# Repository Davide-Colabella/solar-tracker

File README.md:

# Solar Tracker (Arduino UNO Q)

App per Arduino App Lab: pannello a 2 assi (azimut + pitch) che insegue il sole,
si apre quando alla pianta che ha sotto arriva poca luce (fotoresistore),
riconosce la pianta e il suo stato di salute da una foto e la innaffia dal
serbatoio di raccolta quando ne ha bisogno. Una pagina web mostra tutto e
permette di muovere il pannello a mano.

## Sito di presentazione

La landing page Solar Tracker in stile COESA Energy è in [`docs/`](docs/index.html), con immagini e font locali. È distinta dall'interfaccia Arduino in `assets/index.html`.

Indirizzo previsto su GitHub Pages: [davide-colabella.github.io/solar-tracker/](https://davide-colabella.github.io/solar-tracker/).

Per attivare la pubblicazione, un amministratore o un utente con il permesso di gestire GitHub Pages deve aprire **Settings → Pages**, selezionare **Deploy from a branch**, poi **main → /docs → Save**. Il file `.nojekyll` permette di pubblicare direttamente i file statici. I successivi push dei file in `docs/` aggiornano il sito automaticamente.

Per l'anteprima locale: `python3 -m http.server 4173 --directory docs --bind 127.0.0.1`.

La pagina presenta un concept di servizio. La tabella e il configuratore usano le stime dell’analisi economica HackTurin di Davide Colabella (11 ottobre 2026, pp. 5–8): kit principale 349 €, satellite 149 €, software opzionale 48 €/anno, IVA esclusa e pannelli del cliente. Verifica, smontaggio e posa restano da quotare. La torta riguarda un ordine tipo di 4 pannelli: ricavi 796 €, produzione 440,10 €, commissione installatore 119,40 €, altri costi variabili 60 €, margine di contribuzione 176,50 € prima di costi fissi e imposte. Il margine non è un risparmio in bolletta. Il modulo prepara un riepilogo nel browser senza inviare richieste.

```
app.yaml               nome dell'app e brick WebUI
sketch/sketch.ino      microcontrollore: sensori, servo, LED, valvola, sicurezza
sketch/sketch.yaml     librerie
assets/index.html      pagina web (porta 7000)
python/main.py         avvio dell'app sul lato Linux
python/config.py       TUTTA la taratura (coordinate, meccanica, soglie)
python/controller.py   logica di decisione
python/tracker.py      collega telemetria, meteo, modelli, servo e pagina web
python/webui.py        indirizzi della pagina web (/state, /photo, /manual, /auto)
python/solar.py        posizione del sole e ricerca della posa migliore
python/weather.py      previsioni Open-Meteo con cache
python/ai_model.py     interfaccia verso i due modelli AI + sostituti simulati
python/colleague_model.py  carica i modelli ONNX veri da python/models/
python/requirements.txt    librerie Python in più (onnxruntime)
python/irrigation.py   quando e quanto innaffiare
python/demo.py         giornata simulata per le dimostrazioni
python/devices.py      camera della pianta
python/plants.py       profili delle piante (acqua, luce minima, temperatura)
tests/test_logic.py    prove della logica su PC, senza scheda
3d models/             supporto del pannello e scatole da stampare (STEP, STL) + render/
hardware/              schede valvole e INA: schematici, PCB KiCad e render PNG
```

## Tecnologie usate

| Parte | Tecnologia |
|---|---|
| Scheda | **Arduino UNO Q**: microcontrollore STM32U585 (sketch su Zephyr) + processore Qualcomm QRB2210 con Linux (lato Python), sulla stessa scheda |
| Ambiente | **Arduino App Lab**: un'app = sketch + Python + pagina web (`app.yaml`), brick `arduino:web_ui` |
| Microcontrollore | C++ Arduino; driver PWM di **Zephyr** sul timer TIM4 per i servo; I2C software per i sensori |
| Collegamento MCU ↔ Linux | **Arduino_RouterBridge** (chiamate RPC e notifiche in MsgPack) |
| Lato Linux | **Python 3**: libreria standard più `numpy` e `onnxruntime` |
| Pagina web | HTML, CSS e JavaScript senza librerie, servita dal brick WebUI sulla porta 7000 |
| Meteo | API **Open-Meteo** (gratuita, senza chiave), con cache su disco |
| Posizione del sole | calcolo astronomico in `solar.py`, nessun servizio esterno |
| Intelligenza artificiale | due modelli **MobileNetV3-Small** in formato **ONNX**, eseguiti con **ONNX Runtime** (OpenCV come ripiego) |
| Sensori e moduli | Grove Base Shield, 2× Grove **AHT20** (temperatura e umidità), fotoresistore, servo **SG90**, camera USB |
| Meccanica | parti progettate in CAD (STEP) e scatole in STL, stampate in 3D |

## Pinout

**La UNO Q lavora a 3,3 V.** Molti pin digitali sopportano 5 V in ingresso, ma non D3, A0 e A1
(massimo 3,6 V) né gli altri pin analogici quando leggono.

### Con il Grove Base Shield (Seeed), interruttore su 5V

Lo sketch è impostato così (`SHIELD_5V 1`). A 5 V vale una regola: **niente che mandi un
segnale sul pin D3 e niente segnali analogici**. Per questo l'AHT20 della pianta non sta sulla
porta D2 e il fotoresistore si legge dalla sua uscita digitale.

| Porta dello shield | Filo giallo | Filo bianco | Note |
|---|---|---|---|
| **I2C** (una qualsiasi) | AHT20 n.1 "aria esterna", cavo Grove intero | | SDA/SCL (D20/D21), I2C via software |
| **D2** | fotoresistore, uscita **DO** (D2) | **non collegare** (è D3) | rosso → VCC, nero → GND del modulino. AO resta scollegato |
| **D4** | AHT20 n.2 "sotto il pannello", cavo Grove intero | | D4 = SCL, D5 = SDA, I2C via software |
| **D6** | LED luce pianta (D6) | LED meteo (D7) | |
| **D8** | LED stato (D8) | | |
| **A0** | valvole, linea 1 (A0) | linea 2 (A1) | verso l'integrato pilota |
| **A2** | valvole, linea 3 (A2) | linea 4 (A3) | verso l'integrato pilota |
| pin della scheda | servo azimut: **D9** segnale · servo pitch: **D10** segnale | | rosso e marrone all'alimentazione 5 V separata |
| **USB-C** | alimentazione, camera USB | | lato Linux |

Previsti nel firmware ma non collegati: galleggiante (D13), umidità del
terreno (A4, solo a 3,3 V), INA219 (porta I2C).

- I due AHT20 hanno lo stesso indirizzo fisso (0x38): uno sulle porte I2C, l'altro sulla porta D4.
- Il fotoresistore a 5 V dà solo luce o buio; la soglia è la vite blu del modulino. Per avere
  la percentuale serve l'uscita AO su A1, quindi il modulino a 3,3 V oppure un partitore
  (AO → 10 kΩ → A1 → 20 kΩ → GND) e `LIGHT_DIGITAL 0` nello sketch.
- Sui fili rossi dei cavi Grove ci sono 5 V: ai LED non vanno collegati.
- Con l'interruttore su 3.3V: `SHIELD_5V 0`, AHT20 della pianta sulla porta D2, fotoresistore
  con AO su A1.

### LED

Accesi a livello alto. LED nudi: resistenza da 330 Ω – 1 kΩ in serie, catodo a GND.
Chi non serve si disattiva mettendo `-1` al posto del pin nello sketch.

| LED | Pin | Significato |
|---|---|---|
| Stato | D8 | 1 lampo ogni 2 s = tutto ok · 2 lampi = manca un AHT20 · lampeggio veloce = il lato Linux non sta comandando |
| Linee 1–4 | A0, A1, A2, A3 | nella scatola delle valvole: acceso = linea aperta. Sono le uscite vere delle elettrovalvole |
| Luce pianta | D6 | fisso = pannello aperto per dare luce alla pianta · lampeggiante = comando manuale dalla pagina web |
| Meteo | D7 | fisso = piove · lampeggio veloce = sicurezza vento |

Ci sono anche un LED per ciascun asse (`PIN_LED_AZ`, `PIN_LED_PITCH`), spenti di default:
con i servo montati il movimento si vede direttamente.

### Servo ed elettrovalvole

I servo sono pilotati dal timer hardware della scheda (PWM su D9/D10), senza la
libreria Servo, che su questa scheda blocca lo sketch. Solo D9 e D10 hanno quel
timer: su altri pin servirebbe `SERVO_USE_HW_PWM 0` e i servo andrebbero a scatti.

| Filo SG90 | Servo azimut (base) | Servo pitch (inclinazione) |
|---|---|---|
| arancione (segnale) | **D9** | **D10** |
| rosso (+5 V) | +5 V dell'alimentazione separata | +5 V dell'alimentazione separata |
| marrone (GND) | GND dell'alimentazione separata | GND dell'alimentazione separata |

- L'alimentazione separata deve dare 5 V e almeno 2 A. Il suo GND va collegato anche
  a un GND della scheda, altrimenti il segnale non ha riferimento.
- Mai dal 3V3 né dai fili rossi delle porte Grove.
- Un elettrolitico da 470–1000 µF tra 5 V e GND vicino ai servo evita i reset quando partono.
- All'avvio solo il servo di azimut fa la prova 20° → 70° → 20° (`SERVO_SELF_TEST`). Il
  pitch resta fermo: la sua corsa è limitata dal pannello.
- Il pitch è montato al contrario: `PITCH_SERVO_REVERSED 1` nello sketch inverte l'impulso
  (180° − angolo). Il resto del programma usa gli stessi gradi.
- Il servo non sa se sbatte (non ha un ritorno di posizione). La protezione è la corsa
  tarata a mano nello sketch, in gradi della pagina: **135°** = pannello in piano, **65°** =
  alzato al massimo (70° di inclinazione), **150°** = inclinato di 15° dall'altra parte
  (`PITCH_MIN_DEG` / `PITCH_MAX_DEG` = 65 / 150). La scheda rifiuta qualunque angolo fuori corsa, sia da
  Linux sia dalla pagina. Se si rimonta la squadretta del servo, va rifatta la taratura.

Elettrovalvole: quattro linee, su A0, A1, A2 e A3. I pin danno 3,3 V e pochi mA,
quindi comandano solo l'integrato pilota sulla millefori (oggi accende 4 LED,
domani le valvole vere con lo stesso circuito); le valvole hanno la loro
alimentazione. Livello alto = linea aperta (`VALVE_ACTIVE_HIGH`). Con le valvole
vere servono un diodo di ricircolo su ogni bobina, se l'integrato non li ha già,
e valvole che aprano **a pressione zero** (ad azione diretta): con un serbatoio
a caduta molte valvole da irrigazione a 12 V non aprono.

## Alimentazione

```
pannello → step-down → HW-736 → batteria LiPo 3,7 V → convertitore boost 5 V → pin 5V della UNO Q + servo
```

- La UNO Q vuole **5 V stabili, almeno 3 A** (pin 5V o USB-C; in alternativa 7–24 V su VIN).
- L'HW-736 risulta essere un caricatore CN3065: in uscita dà la tensione della
  batteria (3,7–4,2 V), non 5 V, quindi serve un boost a 5 V tra batteria e scheda.
- Lo stesso modulo carica al massimo a 500 mA (circa 2 W): da verificare contro il
  consumo della scheda, che è un computer Linux.
- Alimentando dal pin 5V, la porta USB-C resta libera per la camera.

## Componenti simulati

| Componente | Dove | Come si passa a quello vero |
|---|---|---|
| Elettrovalvole | `sketch.ino` | le uscite funzionano già (LED). Con le valvole vere `#define HAS_VALVE 1`: cambia solo la scritta sulla pagina |
| Sensore di terreno | `sketch.ino` | `#define HAS_SOIL_SENSOR 1` e taratura `SOIL_RAW_DRY` / `SOIL_RAW_WET`. Senza, il fabbisogno è stimato |
| Galleggiante | `sketch.ino` | `#define HAS_TANK_SENSOR 1`. Senza, il livello del serbatoio è stimato dalla pioggia |
| INA219 | `sketch.ino` | niente: viene rilevato da solo all'indirizzo 0x40. Finché manca, la potenza è *stimata* dal modello solare |
| Fotoresistore | `sketch.ino` | è attivo; se non è montato `#define HAS_LIGHT_SENSOR 0` |

## Pagina web

Con l'app in esecuzione: `http://<nome-della-scheda>.local:7000`. Ha due pagine.

**Impianto**
- **Pannello** (riquadro scuro): modalità, motivo, disegno di sole e pannello, copia dei LED.
- **La pianta**: si carica una foto, i due modelli dicono che pianta è e come sta.
  Il tipo imposta il profilo (acqua, luce minima); se ha sete parte subito un'innaffiatura.
- **Luce alla pianta**: lettura del fotoresistore rispetto al minimo della pianta.
- **Irrigazione**: sete, serbatoio, acqua erogata, stato delle quattro linee e comando
  a mano (si scelgono le linee e i secondi, al massimo 60; si richiudono da sole o
  con "Chiudi tutto"; non vale la pausa di 5 minuti dell'automatico, resta il
  blocco a serbatoio vuoto).
- **Le mie piante** (mockup): una scheda per pianta, una per linea (`GARDEN` in
  `config.py`). Per ognuna: luce, temperatura e acqua giudicate con i sensori montati
  (il fotoresistore contro la luce minima della pianta, l'AHT20 sotto il pannello contro la
  sua temperatura massima, il sensore di terreno se c'è, altrimenti la sete stimata), il
  fabbisogno di oggi e la **prossima innaffiatura stimata**: consumo scalato con l'aria secca,
  dose divisa per linea, pausa minima, rimandata fuori dalle ore calde salvo urgenza, bloccata
  a serbatoio vuoto. È una stima: per ora l'acqua vera segue la pianta riconosciuta dalla foto,
  con la dose divisa tra le quattro linee.
- **Muovi il pannello a mano**: due cursori e pose rapide. Torna in automatico con
  il pulsante o dopo 10 minuti (`MANUAL_TIMEOUT_S`). Il vento forte vince comunque.

**Prova componenti** (per il banco, non per la demo)
- "Avvia la prova" ferma l'automatismo (anche la sicurezza vento) e tiene sveglia
  la scheda; si chiude con il pulsante o da sola dopo 10 minuti (`DEBUG_TIMEOUT_S`).
- **Servo**: angolo diretto del servo, senza passare dai calcoli del sole. Azimut 0–180°,
  pitch 65–150° (la corsa tarata, 135° = in piano).
- **Elettrovalvole**: una linea alla volta, tutte insieme o una dopo l'altra, 3 secondi l'una.
- **LED**: accende un LED alla volta (stato, pianta, meteo), tutti, o in sequenza.
- **Sensori**: valori in diretta dei due AHT20, del fotoresistore e
  dei componenti facoltativi, ognuno con "risponde", "non risponde" o "non montato".
- **Fotoresistore**: lettura grezza e taratura (buio, piena luce).
- **Camera e modelli**: scatto di prova e stato dei due modelli (vero o simulato).
- **Scheda**: età degli ultimi dati, a che punto è lo sketch, ultimi messaggi `[MCU]`.

I comandi partono subito: la pagina sveglia il ciclo del lato Linux. I servo però si
muovono a rampa, 30°/s (`SERVO_SPEED_DEG_S`).

## Modelli AI

Le cartelle dei modelli sono incluse nel progetto: [PlantWatch](ai-models/plantwatch/README.md)
per la condizione della pianta e [PlantNet-300K](ai-models/plantnet300k-mobilenetv3-small/README.md)
per la specie. L'[overview AI](ai-models/README.md) riporta dataset, accuracy, dimensioni e
stato dell'integrazione. Il loader usa PlantWatch per la salute e PlantNet-300K
per la specie.

Due modelli ONNX in `python/models/`, dichiarati in `config.py` (`HEALTH_MODEL_*`,
`PLANT_MODEL_*`). Entrambi sono MobileNetV3-Small con ingresso 224×224; le foto
vengono normalizzate con i valori ImageNet (`MODEL_MEAN`, `MODEL_STD`).
PlantWatch usa il ridimensionamento bilineare diretto a 224×224; il riconoscitore
di specie mantiene il lato corto a 256 e il ritaglio centrale a 224.

- **Tipo di pianta** (`plantnet_mobilenetv3.onnx`): 1081 specie del dataset
  Pl@ntNet-300K. I nomi scientifici sono in `plantnet_labels.txt`, uno per riga
  nell'ordine delle uscite (id di specie in ordine crescente, come nel codice
  ufficiale del dataset). **Non conosce basilico, pomodoro, peperone, spinacio**;
  conosce per esempio fragola, lattuga, zucca e zucchina, lavanda, geranio,
  calendula, tagete, piante grasse (Sedum, Lithops, cactus), felci e molte piante
  da interno (Anthurium, Alocasia, Peperomia, Fittonia, Zamioculcas, Schefflera,
  Tradescantia). Se la specie è incerta ma il genere è sicuro, vale il genere.
  Il profilo (acqua, luce, temperatura) si sceglie dal genere: tabella `GENUS`
  in `plants.py`; un genere senza profilo usa i valori generici.
- **Salute — PlantWatch** (`plantwatch.onnx`): due uscite, nell'ordine
  `healthy` (0) e `wilted` (1), confermato da `plantwatch.json`. Il modello è
  addestrato su Houseplants e usa `HEALTH_MODEL_DIRECT_RESIZE = True`.
- `HEALTH_OK_KEYWORDS` e `HEALTH_THIRSTY_KEYWORDS` dicono quali etichette
  significano "sana" e "ha sete" (quest'ultima fa partire un'innaffiatura).
- Per eseguire i modelli servono `onnxruntime` e `Pillow`, elencati in
  `python/requirements.txt` (App Lab lo installa al primo avvio, serve la rete).
  Se manca si prova con OpenCV; se non c'è nemmeno quello i modelli restano
  simulati, e la pagina lo scrive.

## Logica

A ogni decisione, in ordine di priorità:

1. **SICUREZZA** – raffica prevista ≥ 10 m/s: pannello piatto per almeno 10 minuti.
2. **MANUALE** – posa scelta dalla pagina web.
3. **NOTTE** – piatto.
4. **LUCE_PIANTA** – il fotoresistore legge meno del minimo della pianta
   (`light_min_pct` in `plants.py`): il pannello si apre un passo alla volta, da
   puntato al sole a messo di taglio, così la luce passa. Quando la luce supera
   il minimo + `LIGHT_HYSTERESIS_PCT`, o sotto il pannello fa più caldo del
   massimo della pianta, si richiude un passo alla volta.
5. **PRODUZIONE** – posa che massimizza l'irraggiamento previsto sul pannello:
   col sereno insegue il sole, col coperto si mette quasi piatto, con la pioggia
   resta inclinato almeno 10° per far scolare l'acqua.

La pioggia prevista viene confermata dall'umidità dell'AHT20 esterno. Se il lato
Linux smette di rispondere per 5 minuti il microcontrollore porta il pannello
in piano da solo.

Taratura della luce, dalla pagina web (riquadro "Luce alla pianta"): coprire il
sensore e premere "adesso è buio", scoprirlo e premere "adesso è piena luce". Da
lì la scala va da 0 (buio) a 100 (piena luce) qualunque sia il modulino, anche
se legge al contrario; resta salvata tra un avvio e l'altro. Le soglie delle
piante (`light_min_pct` in `plants.py`) sono percentuali di questa scala.

## Dimostrazione e basso consumo (`config.py`)

- `DEMO_MODE = True`: sole e meteo simulati, una giornata in circa 4 minuti
  (sereno, coperto, pioggia, raffiche). Sensori, fotoresistore, servo e LED sono
  quelli veri. **Rimettere `False` per l'uso reale.**
- `LOW_POWER_MODE = True` (vale solo con `DEMO_MODE = False`): l'impianto si
  sveglia ogni `WAKE_PERIOD_S` (30 minuti), legge i sensori, guarda le previsioni,
  decide, muove il pannello puntando dove sarà il sole a metà intervallo, poi
  toglie il segnale ai servo, spegne i LED e ferma le letture. Una foto o un
  comando manuale dalla pagina lo svegliano subito. Il processore Linux della
  scheda resta acceso: si risparmia su servo, LED e microcontrollore.

## Irrigazione

Il fabbisogno dipende dalla pianta riconosciuta (`water_ml_day` in `plants.py`).

- **Senza sensore di terreno**: bilancio idrico. Il fabbisogno giornaliero viene
  scalato con la secchezza dell'aria misurata dall'AHT20 sotto il pannello e si
  eroga una dose (150 ml) ogni volta che il debito accumulato la raggiunge.
- **Con il sensore di terreno**: si innaffia sotto la soglia `soil_min_pct` della pianta.
- Si evita il pieno sole (si rimanda alla sera, salvo urgenza), si aspetta
  30 minuti tra due dosi e non si supera il doppio del fabbisogno giornaliero.
- Il serbatoio si riempie con la pioggia (`COLLECTOR_AREA_M2`); a serbatoio vuoto
  non si apre e il log avvisa.
- Le linee sono quattro (`VALVE_LINES`): a ogni innaffiatura la dose viene divisa
  tra le linee, aperte una dopo l'altra.
- Sul microcontrollore ogni linea si richiude comunque da sola: al massimo 60 s
  per apertura e 5 minuti di pausa tra due aperture, anche se Linux si blocca.

Da tarare: `VALVE_FLOW_ML_S` (portata reale di una linea aperta), capienza del
serbatoio e superficie di raccolta. `RAIN_ON_PLANT_FRACTION` dice quanta pioggia
arriva alla pianta: è 0, cioè il pannello la copre.

## Diagnostica

Lo sketch non usa il monitor seriale: manda i suoi messaggi al lato Linux, che li
scrive nella console Python con il prefisso `[MCU]` (stato dei componenti ogni 30 s).
Se la telemetria non arriva, la console Python dice a che punto dell'avvio si è
fermato lo sketch.

## Configurazione

Tutta la taratura sta in due file: `sketch/sketch.ino` per il microcontrollore e
`python/config.py` per il lato Linux. Alcuni valori esistono in tutti e due e vanno
cambiati insieme (indicati con ↔).

### Sketch (`sketch/sketch.ino`)

| Impostazione | Valore | A cosa serve |
|---|---|---|
| `SHIELD_5V` | 1 | interruttore del Grove Base Shield su 5V (0 = su 3.3V, cambia la piedinatura) |
| `HAS_SERVO_AZ`, `HAS_SERVO_PITCH` | 1, 1 | servo montati; con 0 l'asse è simulato |
| `AZ_DETACH_IDLE`, `PITCH_DETACH_IDLE` | 1, 0 | stacca il segnale ad asse fermo; il pitch resta in tensione per reggere il pannello |
| `SERVO_USE_HW_PWM` | 1 | impulsi dal timer TIM4 (solo D9/D10); 0 = dal loop, a scatti |
| `SERVO_SELF_TEST` | 1 | prova 20° → 70° → 20° all'avvio, solo sull'azimut |
| `AZ_MIN_DEG`/`AZ_MAX_DEG` | 0 / 180 | corsa del servo di base |
| `PITCH_MIN_DEG`/`PITCH_MAX_DEG` | 65 / 150 | corsa tarata del pitch (↔ `TILT_MAX_DEG` / `TILT_MIN_DEG`) |
| `AZ_SERVO_REVERSED`, `PITCH_SERVO_REVERSED` | 0, 1 | servo montato al contrario: impulso a 180° − angolo |
| `SERVO_US_MIN`/`SERVO_US_MAX` | 500 / 2400 µs | larghezza dell'impulso a 0° e 180° (SG90) |
| `SERVO_SPEED_DEG_S` | 30 | velocità della rampa (↔ `SERVO_SPEED_DEG_S`) |
| `PLANT_AHT_ON_SOFT_I2C` | 1 | AHT20 della pianta sulla porta D4 (0 = connettore Qwiic) |
| `MAIN_I2C_SOFT` | 1 | porte I2C dello shield in I2C software (non serve pull-up esterno) |
| `HAS_LIGHT_SENSOR`, `LIGHT_DIGITAL` | 1, = `SHIELD_5V` | fotoresistore montato; a 5 V si legge solo l'uscita DO |
| `HAS_VALVE` | 0 | 0 = LED al posto delle valvole (cambia solo la scritta sulla pagina) |
| `VALVE_ACTIVE_HIGH` | 1 | livello alto = linea aperta |
| `VALVE_MAX_OPEN_MS`, `VALVE_MIN_PAUSE_MS` | 60 s, 5 min | protezioni delle valvole, valide anche se Linux si blocca |
| `HAS_SOIL_SENSOR`, `HAS_TANK_SENSOR` | 0, 0 | sensore di terreno e galleggiante (oggi stimati) |
| `PIN_LED_*` | vedi Pinout | `-1` = LED non montato |
| `COMMS_TIMEOUT_MS` | 5 min | senza comandi da Linux il pannello va in posa di sicurezza |

### Lato Linux (`python/config.py`)

| Gruppo | Impostazioni | Valori attuali |
|---|---|---|
| Luogo | `LATITUDE`, `LONGITUDE` | Roma (41,90; 12,50) |
| Azimut | `AZ_REF_DEG`, `AZ_SERVO_AT_REF`, `AZ_SERVO_DIR`, `AZ_SERVO_MIN/MAX` | servo a 90° = pannello verso sud; corsa 0–180 = da est a ovest |
| Pitch | `PITCH_SERVO_AT_FLAT`, `PITCH_SERVO_DIR`, `TILT_MIN_DEG`, `TILT_MAX_DEG` | servo 135° = in piano, direzione −1 (si alza scendendo verso 65°), inclinazione da −15° a 70° |
| Movimento | `MOVE_DEADBAND_DEG`, `SERVO_SPEED_DEG_S` | 1,5°; 30°/s |
| Pioggia | `RAIN_NOW_MM_H`, `RAIN_CONFIRM_RH`, `RAIN_SOON_PROB`, `RUNOFF_TILT_DEG` | 0,3 mm/h; 75 % UR; 70 %; 10° |
| Vento | `WIND_STOW_MS`, `WIND_RELEASE_MS`, `STOW_HOLD_S`, `STOW_TILT_DEG` | raffica 10 m/s → piatto per almeno 10 minuti, si rilascia sotto 7 m/s |
| Notte | `NIGHT_ELEVATION_DEG`, `NIGHT_TILT_DEG` | sole sotto −1° → piatto |
| Meteo | `WEATHER_REFRESH_S`, `WEATHER_MAX_AGE_S` | ogni 30 minuti, validità 6 ore |
| Luce alla pianta | `PLANT_LIGHT_ENABLED`, `LIGHT_STEP`, `LIGHT_HYSTERESIS_PCT` | attiva, un quarto di corsa per decisione, isteresi 15 punti |
| Modelli AI | `HEALTH_MODEL_*`, `PLANT_MODEL_*`, `MODEL_*`, `*_KEYWORDS`, `*_MIN_CONFIDENCE` | vedi "Modelli AI" |
| Le mie piante | `GARDEN` | basilico, pomodoro, fragola, lavanda (linee 1–4): **da cambiare con le tue** |
| Irrigazione | `VALVE_LINES`, `VALVE_FLOW_ML_S`, `WATER_DOSE_ML`, `WATER_MAX_OPEN_S`, `WATER_MIN_INTERVAL_S`, `WATER_DAILY_CAP_FACTOR` | 4 linee, 10 ml/s (**da misurare**), 150 ml a dose, max 60 s, pausa 30 minuti |
| Serbatoio | `TANK_CAPACITY_ML`, `COLLECTOR_AREA_M2`, `COLLECTOR_EFFICIENCY`, `RAIN_ON_PLANT_FRACTION` | 5 l; la pianta non riceve pioggia (0) |
| Cadenze | `DECISION_PERIOD_S`, `MANUAL_TIMEOUT_S`, `DEBUG_TIMEOUT_S` | una decisione al minuto; manuale e prova durano al massimo 10 minuti |
| Basso consumo | `LOW_POWER_MODE`, `WAKE_PERIOD_S` | attivo, risveglio ogni 30 minuti (solo fuori dalla demo) |
| Dimostrazione | `DEMO_MODE`, `DEMO_SPEED`, `DEMO_STEP_S` | **attiva**: una giornata in circa 4 minuti |
| Camera | `PLANT_CAMERA_SOURCE` | prima camera USB trovata |

`TILT_MIN_DEG` negativo vuol dire che il pannello si inclina anche dall'altra parte (fino a
15°): il programma può scegliere quelle pose se rendono di più. Con al massimo 70° di inclinazione, a mezzogiorno d'estate il
pannello non riesce a mettersi del tutto di taglio: per la luce alla pianta si avvicina il più
possibile.

## Modelli 3D

Nella cartella `3d models/`, con i render in `3d models/render/`. Misure in millimetri.

**Supporto del pannello** (STEP, da aprire nel CAD ed esportare per la stampa)

| | | |
|---|---|---|
|  |  |  |
| `01_Base_palo.step` · 90 × 70 × 90<br>base fissata al palo | `02_Forcella_rotante.step` · 37 × 35 × 83<br>gira attorno al palo (azimut) | `03_Telaio_pannello_90x60.step` · 97 × 67 × 21<br>telaio del pannello 90 × 60, si inclina (pitch) |

**Scatole** (STL, pronte per lo slicer)

| | | |
|---|---|---|
|  |  | |
| `scatola1_arduino_corpo.stl` · 80 × 62 × 43<br>scatola della UNO Q con lo shield | `scatola1_arduino_coperchio.stl` · 80 × 62 × 5 | |
|  |  | |
| `scatola2_led_corpo.stl` · 50 × 40 × 28<br>scatola della scheda dei LED e delle valvole, fatta dalla collega | `scatola2_led_coperchio.stl` · 47 × 37 × 6 | |

**Schede elettroniche** (progetti KiCad in `hardware/`)

| Controllo elettrovalvole | Monitor tensione e corrente |
|---|---|
|  |  |
| [Progetto KiCad](hardware/valve-controller/valve-controller.kicad_pro) · 80 × 55 mm<br>L293D, quattro canali per elettrovalvole a 5 V, numerati da 1 a 4. [Collegamenti](schema.md). | [Progetto KiCad](hardware/ina-panel-monitor/ina-panel-monitor.kicad_pro) · 60 × 45 mm<br>INA219 dopo il DC/DC: ramo a 5 V, limite di progetto 2 A, I²C a 3,3 V. [Documentazione](hardware/ina-panel-monitor/README.md). |

## Prove

```
python tests/test_logic.py
python tests/test_models.py
```

Girano su PC con Python 3.10 o successivo, microcontrollore e meteo simulati.
`test_models.py` richiede le dipendenze di `python/requirements.txt` e controlla
preprocessing, etichette, foto con EXIF e inferenza PlantWatch reale.

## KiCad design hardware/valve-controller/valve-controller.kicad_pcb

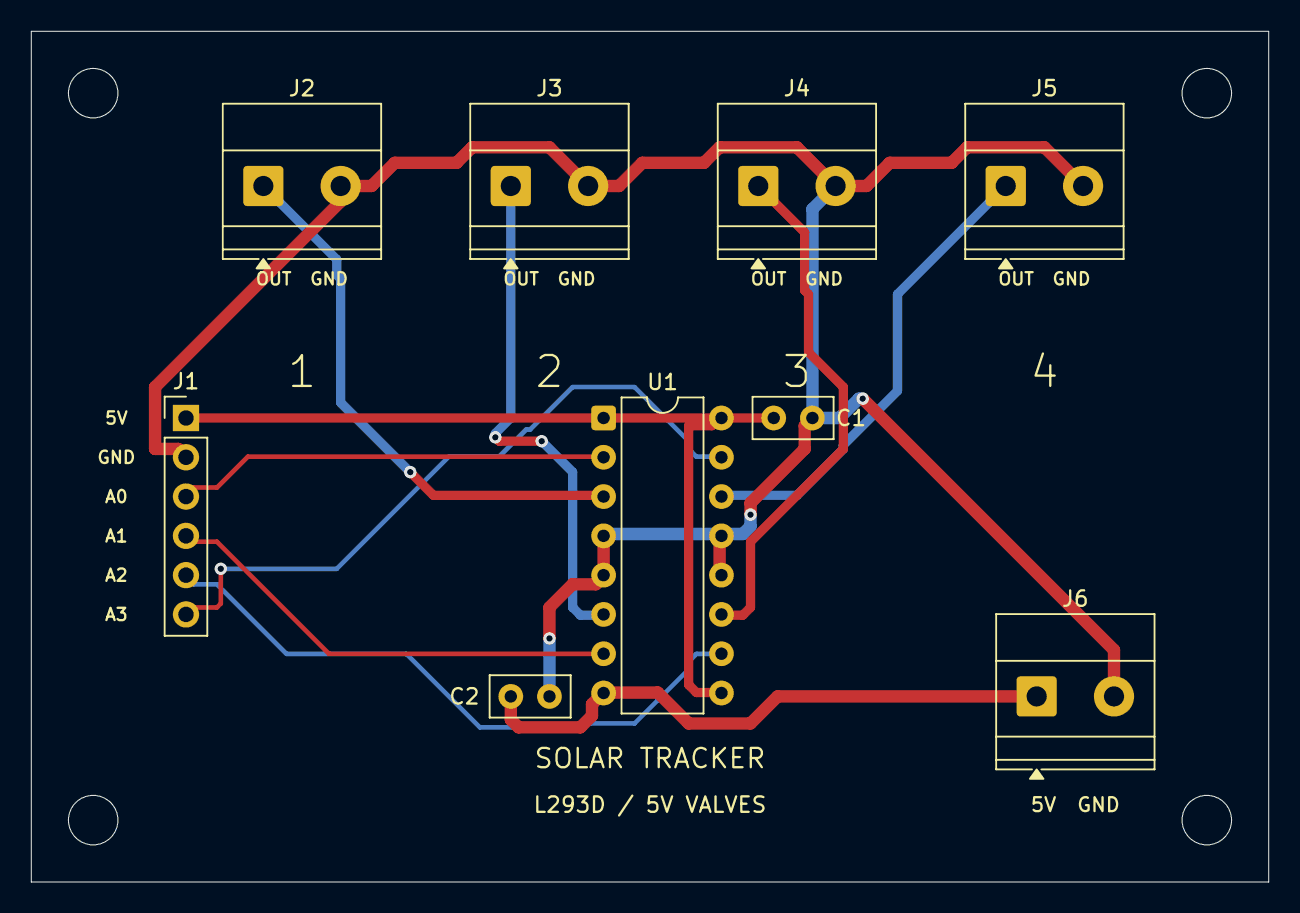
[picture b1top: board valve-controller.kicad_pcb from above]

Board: 2 copper layers, 80.0 x 55.0 mm, 13 parts (0 on the bottom side), 11 nets.

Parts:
C1, C2: 100nF; C_Disc_D5.0mm_W2.5mm_P2.50mm
H1, H2, H3, H4: M3; MountingHole_3.2mm_M3
J1: UNO Q; PinHeader_1x06_P2.54mm_Vertical
J2: Valve 1; TerminalBlock_Phoenix_MKDS-1,5-2_1x02_P5.00mm_Horizontal
J3: Valve 2; TerminalBlock_Phoenix_MKDS-1,5-2_1x02_P5.00mm_Horizontal
J4: Valve 3; TerminalBlock_Phoenix_MKDS-1,5-2_1x02_P5.00mm_Horizontal
J5: Valve 4; TerminalBlock_Phoenix_MKDS-1,5-2_1x02_P5.00mm_Horizontal
J6: 5V DC input; TerminalBlock_Phoenix_MKDS-1,5-2_1x02_P5.00mm_Horizontal
U1: L293D; DIP-16_W7.62mm

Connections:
/+5V: C1.1, J1.1, U1.1, U1.9, U1.16
/+5V_VALVES: C2.1, J6.1, U1.8
/A0: J1.3, U1.2
/A1: J1.4, U1.7
/A2: J1.5, U1.10
/A3: J1.6, U1.15
/GND: C1.2, C2.2, J1.2, J2.2, J3.2, J4.2, J5.2, J6.2, U1.4, U1.5, U1.12, U1.13
/OUT1: J2.1, U1.3
/OUT2: J3.1, U1.6
/OUT3: J4.1, U1.11
/OUT4: J5.1, U1.14

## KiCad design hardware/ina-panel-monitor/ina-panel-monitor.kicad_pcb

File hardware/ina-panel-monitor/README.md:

# Solar Tracker — INA panel monitor

A standalone INA219 board for measuring voltage and current **after an external DC/DC converter**. The converter and rooftop panel are not part of this PCB.

| Characteristic | Design |
| --- | --- |
| Measured supply | Regulated 5 V DC |
| Continuous current | 2 A maximum design target |
| Sensor | INA219BIDR, SOIC-8 |
| Shunt | 0.1 Ω, 1%, at least 1 W, 2512 |
| Logic supply / I²C | 3.3 V / address `0x40` |
| PCB | 60 × 45 mm, two copper layers, 1.6 mm thickness |
| Main power traces | 2 mm; specify at least 35 µm copper |

These are prototype design assumptions, not specifications inferred from the panel's remaining 80% output. Select the external DC/DC only after obtaining the panel's Voc/Isc and required load power. This board must not be connected directly to the unknown rooftop panel: the INA219 has a 26 V maximum operating bus voltage. [TI INA219 datasheet](https://www.ti.com/lit/ds/symlink/ina219.pdf).

## Connections

```text
PV panel → external DC/DC → J1 → shunt R1 → J2 → 5 V load
                                      ↓
                                    INA219 → Arduino I²C
```

| Connector | Pin 1 | Pin 2 | Pin 3 | Pin 4 |
| --- | --- | --- | --- | --- |
| J1 — FROM DC/DC | +5 V input | GND | — | — |
| J2 — TO LOAD | Positive output | GND | — | — |
| J3 — Arduino | 3.3 V | GND | SDA | SCL |

All grounds are shared; this is not an isolated measurement board. J3 supplies the sensor logic separately from the measured 5 V path. Keep SDA/SCL at 3.3 V; the existing project's 5 V shield pullups need a compatible bus or level translation. Do not power J3 from 5 V while using the documented 3.3 V interface.

JP1 is open by default. Bridge it to enable the two local 4.7 kΩ pullups when the host bus does not already provide suitable pullups. A0 and A1 are tied to GND, selecting `0x40`.

## Measurement and firmware

The existing `sketch/sketch.ino` uses address `0x40` and `INA219_SHUNT_OHM = 0.1f`, matching this board. It reads bus voltage at the load side of the shunt and calculates current from the shunt voltage. Python already computes delivered power as `bus_v * current_ma / 1000`.

At 2 A the shunt drops 0.2 V and dissipates 0.4 W: a 5.0 V input therefore gives approximately 4.8 V at J2, before wiring losses. R1 must be a power current-sense resistor; a suitable family is [Vishay WSLT2512](https://www.vishay.com/doc/?30121=), in the 0.1 Ω / 1% / 1 W variant. The filter uses two 10 Ω resistors and a 100 nF differential capacitor. Sense tracks branch separately from the shunt pads; the 3.3 V supply has 100 nF and 1 µF bypass capacitors.

## Detecting reduced production

After the converter, the reading depends on load demand, converter losses and regulation. A lightly loaded system can show low power even with a clean panel. Compare measurements with a clean-panel baseline under similar irradiance, orientation, temperature and load; a drop is an indication to investigate, not proof of dirt. The firmware's current light/dark input is insufficient for quantitative irradiance comparisons: use a calibrated continuous light measurement for this purpose. A panel's existing 80% performance must be included in its baseline.

## KiCad and 3D

Open `ina-panel-monitor.kicad_pro`; the schematic and fully routed board share the same name. `SolarTracker.kicad_sym` and `sym-lib-table` supply the local schematic symbols. Install the standard KiCad 10 footprint and 3D libraries to view the assembled board.

- `ina-panel-monitor-3d.png`: rendered board.

Export schematic previews, a BOM and an assembled STEP model directly from KiCad when needed. JP1 is a solder bridge, not a component to purchase.

The design passed ERC and DRC with no violations, unconnected items or schematic parity issues when created. Reports can be regenerated in KiCad. These checks verify CAD rules and schematic agreement; current capability, heating and measurement accuracy still require tests on the assembled prototype.

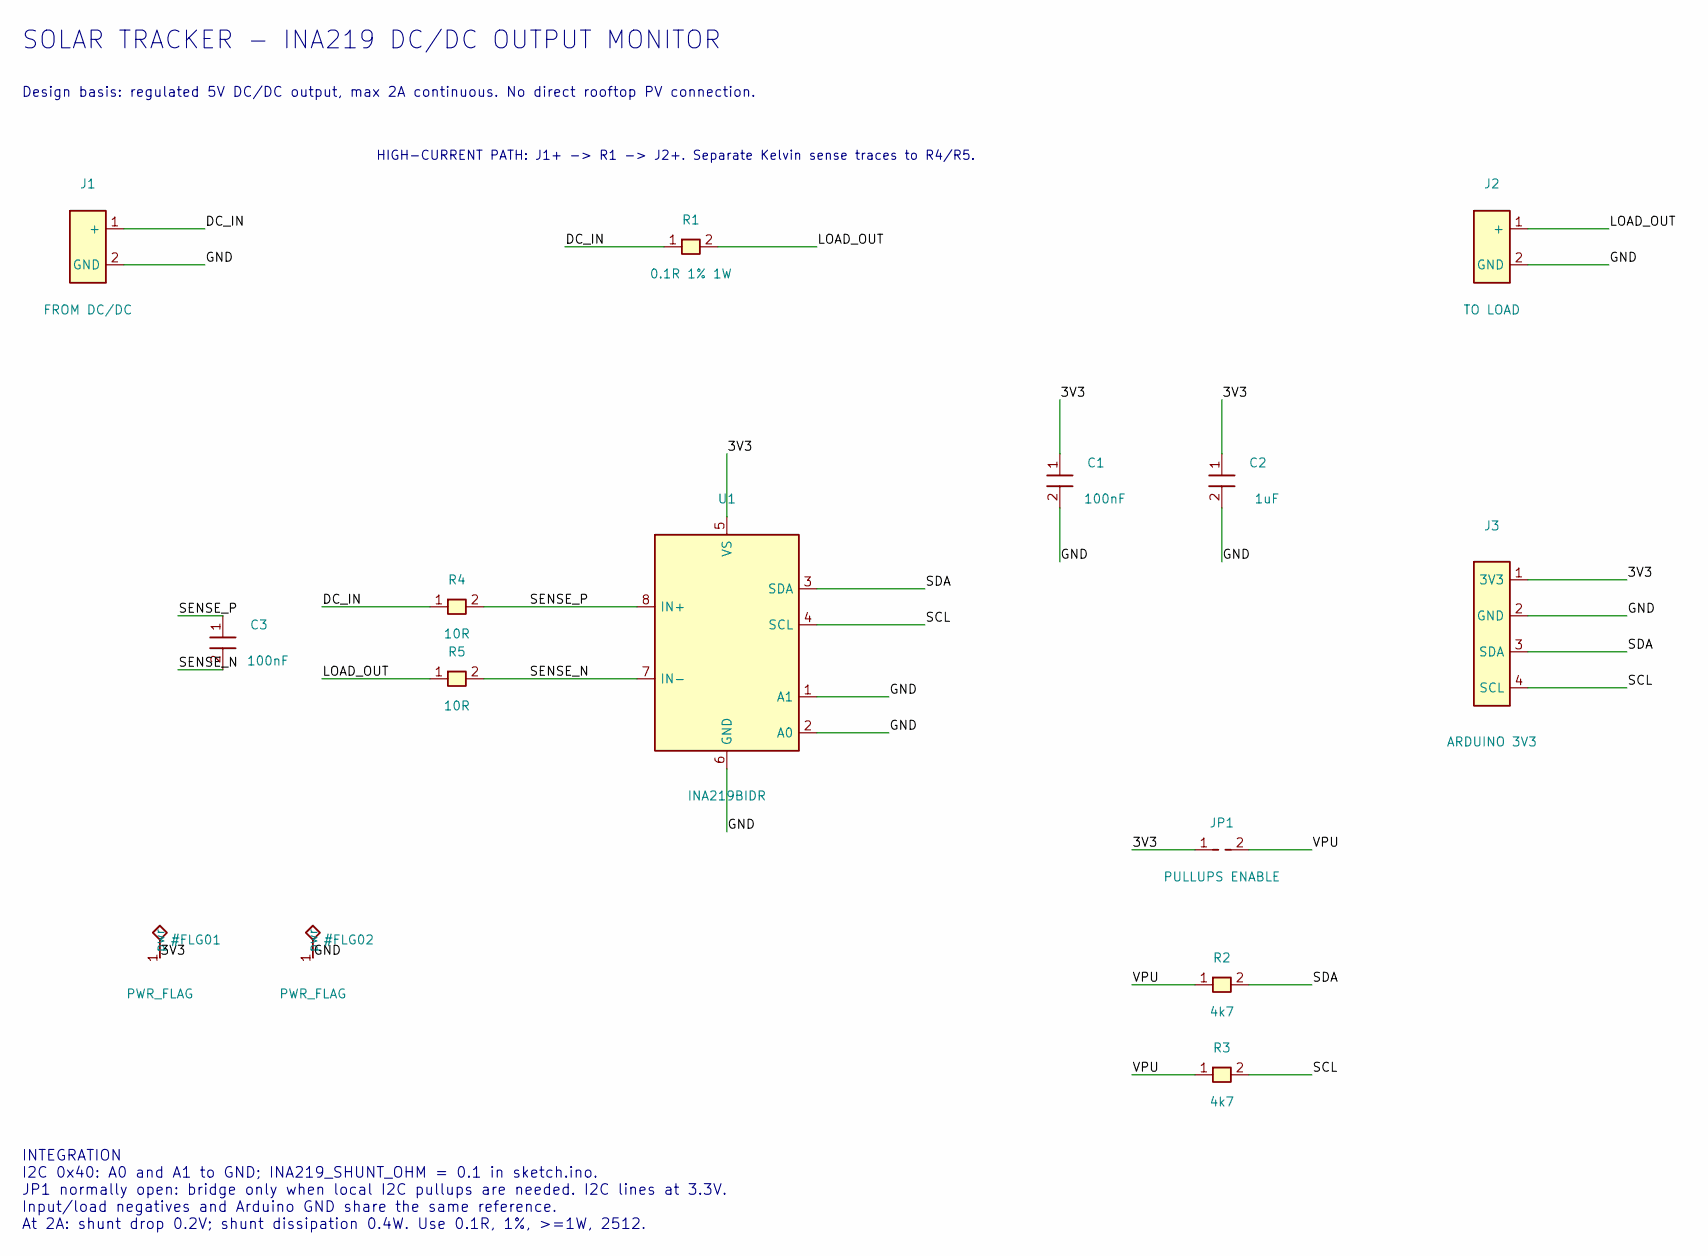
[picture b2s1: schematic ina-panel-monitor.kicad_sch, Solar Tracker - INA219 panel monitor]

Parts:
C1, C3: 100nF; C_0805_2012Metric
C2: 1uF; C_0805_2012Metric
J1: FROM DC/DC; TerminalBlock_Phoenix_MKDS-1,5-2_1x02_P5.00mm_Horizontal
J2: TO LOAD; TerminalBlock_Phoenix_MKDS-1,5-2_1x02_P5.00mm_Horizontal
J3: ARDUINO 3V3; PinHeader_1x04_P2.54mm_Vertical
JP1: PULLUPS ENABLE; SolderJumper-2_P1.3mm_Open_Pad1.0x1.5mm
R1: 0.1R 1% 1W; R_2512_6332Metric
R2, R3: 4k7; R_0603_1608Metric
R4, R5: 10R; R_0603_1608Metric
U1: INA219BIDR; SOIC-8_3.9x4.9mm_P1.27mm

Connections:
/3V3: C1.1, C2.1, J3.1 (3V3), JP1.1, U1.5 (VS)
/DC_IN: J1.1 (+), R1.1, R4.1
/GND: C1.2, C2.2, J1.2 (GND), J2.2 (GND), J3.2 (GND), U1.1 (A1), U1.2 (A0), U1.6 (GND)
/LOAD_OUT: J2.1 (+), R1.2, R5.1
/SCL: J3.4 (SCL), R3.2, U1.4 (SCL)
/SDA: J3.3 (SDA), R2.2, U1.3 (SDA)
/SENSE_N: C3.2, R5.2, U1.7 (IN-)
/SENSE_P: C3.1, R4.2, U1.8 (IN+)
/VPU: JP1.2, R2.1, R3.1

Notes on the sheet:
SOLAR TRACKER - INA219 DC/DC OUTPUT MONITOR
Design basis: regulated 5V DC/DC output, max 2A continuous. No direct rooftop PV connection.
HIGH-CURRENT PATH: J1+ -> R1 -> J2+. Separate Kelvin sense traces to R4/R5.
INTEGRATION I2C 0x40: A0 and A1 to GND; INA219_SHUNT_OHM = 0.1 in sketch.ino. JP1 normally open: bridge only when local I2C pullups are needed. I2C lines at 3.3V. Input/load negatives and Arduino GND share the same reference. At 2A: shunt drop 0.2V; shunt dissipation 0.4W. Use 0.1R, 1%, >=1W, 2512.

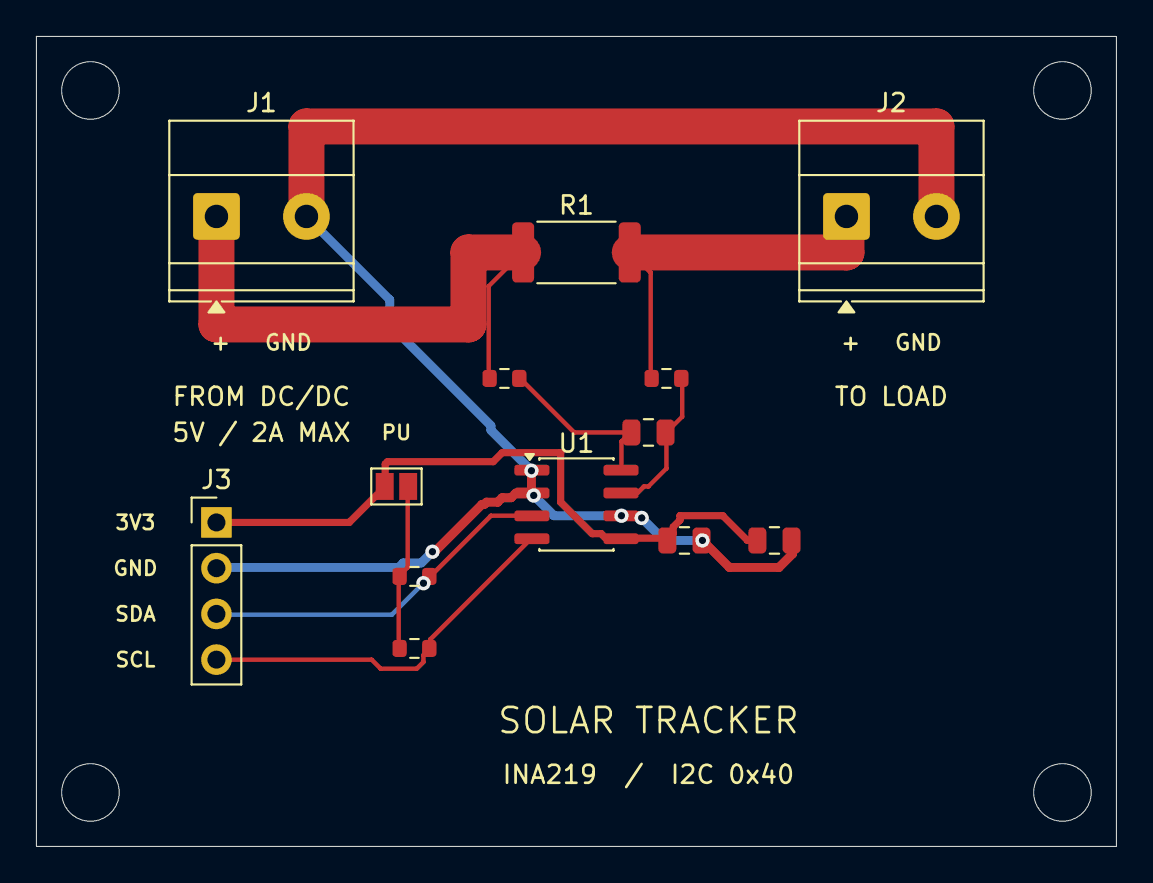
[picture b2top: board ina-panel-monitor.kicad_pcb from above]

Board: 2 copper layers, 60.0 x 45.0 mm, 17 parts (0 on the bottom side), 9 nets.

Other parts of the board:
H1, H2, H3, H4: M3; MountingHole_3.2mm_M3
